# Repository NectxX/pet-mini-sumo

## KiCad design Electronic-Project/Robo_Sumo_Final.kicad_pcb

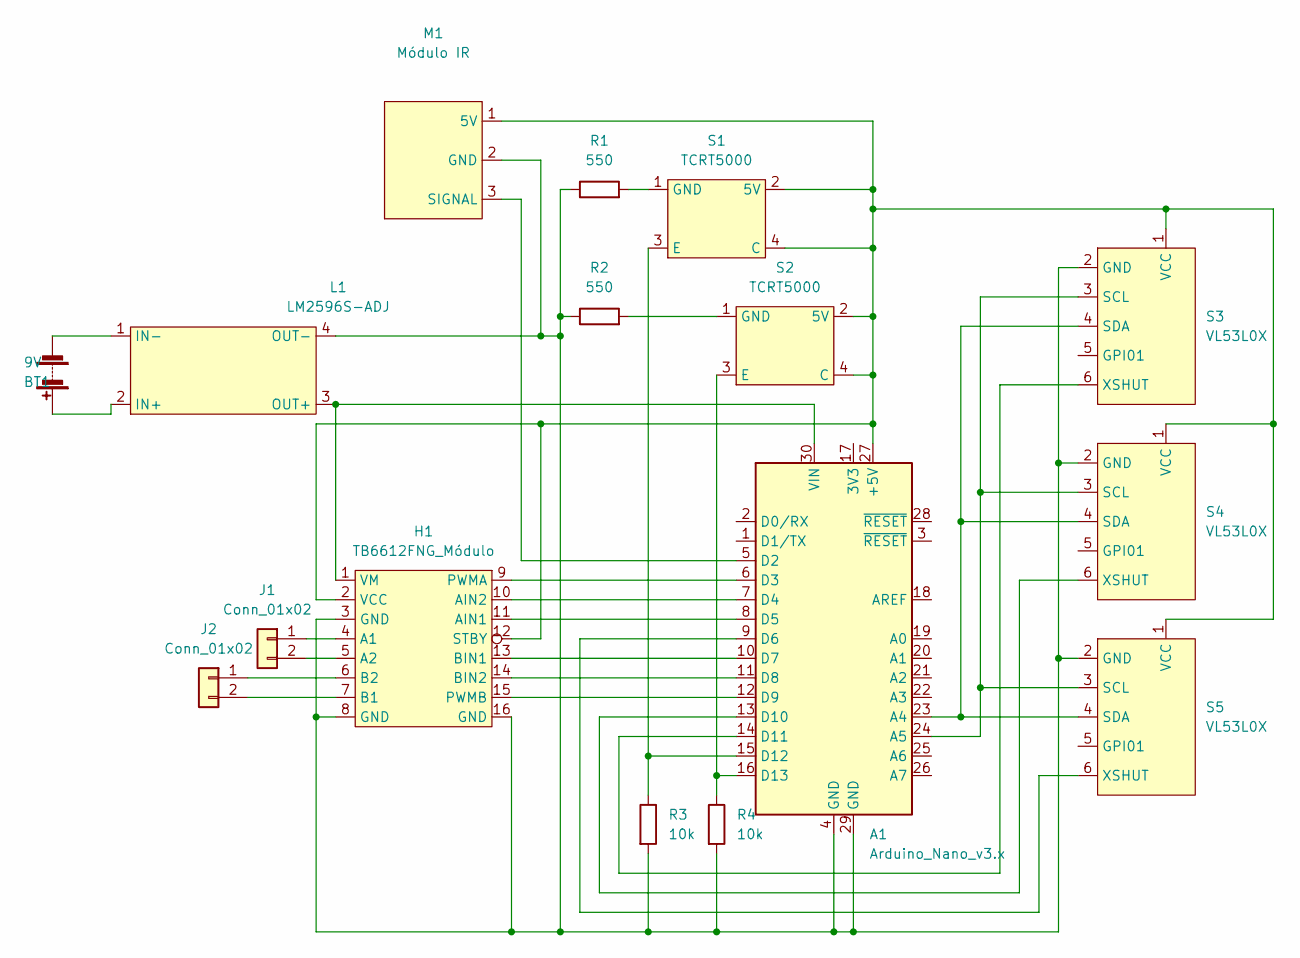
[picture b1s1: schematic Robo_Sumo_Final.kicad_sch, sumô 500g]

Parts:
A1: Arduino_Nano_v3.x; Arduino_Nano
BT1: 9V; PinHeader_1x02_P2.54mm_Vertical
H1: TB6612FNG_Módulo; TB6612FNG
J1, J2: Conn_01x02; PinHeader_1x02_P2.54mm_Vertical
L1: LM2596S-ADJ; LM2596
M1: Módulo IR; PinHeader_1x03_P2.54mm_Vertical
R1, R2: 550; R_Axial_DIN0207_L6.3mm_D2.5mm_P15.24mm_Horizontal
R3, R4: 10k; R_Axial_DIN0207_L6.3mm_D2.5mm_P15.24mm_Horizontal
S1, S2: TCRT5000
S3, S4, S5: VL53L0X; PinHeader_1x06_P2.54mm_Vertical

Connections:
unnamed: A1.5 (D2), M1.3 (SIGNAL)
unnamed: A1.6 (D3), H1.9 (PWMA)
unnamed: A1.7 (D4), H1.10 (AIN2)
unnamed: A1.8 (D5), H1.11 (AIN1)
unnamed: A1.9 (D6), S5.6 (XSHUT)
unnamed: A1.10 (D7), H1.13 (BIN1)
unnamed: A1.11 (D8), H1.14 (BIN2)
unnamed: A1.12 (D9), H1.15 (PWMB)
unnamed: A1.13 (D10), S4.6 (XSHUT)
unnamed: A1.14 (D11), S3.6 (XSHUT)
unnamed: A1.15 (D12), R3.1, S1.3 (E)
unnamed: A1.16 (D13), R4.1, S2.3 (E)
unnamed: A1.23 (A4), S3.4 (SDA), S4.4 (SDA), S5.4 (SDA)
unnamed: A1.24 (A5), S3.3 (SCL), S4.3 (SCL), S5.3 (SCL)
unnamed: A1.27 (+5V), H1.2 (VCC), H1.12 (STBY), M1.1 (5V), S1.2 (5V), S1.4 (C), S2.2 (5V), S2.4 (C), S3.1 (VCC), S4.1 (VCC), S5.1 (VCC)
unnamed: A1.4 (GND), A1.29 (GND), H1.3 (GND), H1.8 (GND), H1.16 (GND), L1.4 (OUT-), M1.2 (GND), R1.1, R2.1, R3.2, R4.2, S3.2 (GND), S4.2 (GND), S5.2 (GND)
unnamed: A1.30 (VIN), H1.1 (VM), L1.3 (OUT+)
unnamed: BT1.1 (+), L1.2 (IN+)
unnamed: BT1.2 (-), L1.1 (IN-)
unnamed: H1.4 (A1), J1.1
unnamed: H1.5 (A2), J1.2
unnamed: H1.6 (B2), J2.1
unnamed: H1.7 (B1), J2.2
unnamed: R1.2, S1.1 (GND)
unnamed: R2.2, S2.1 (GND)

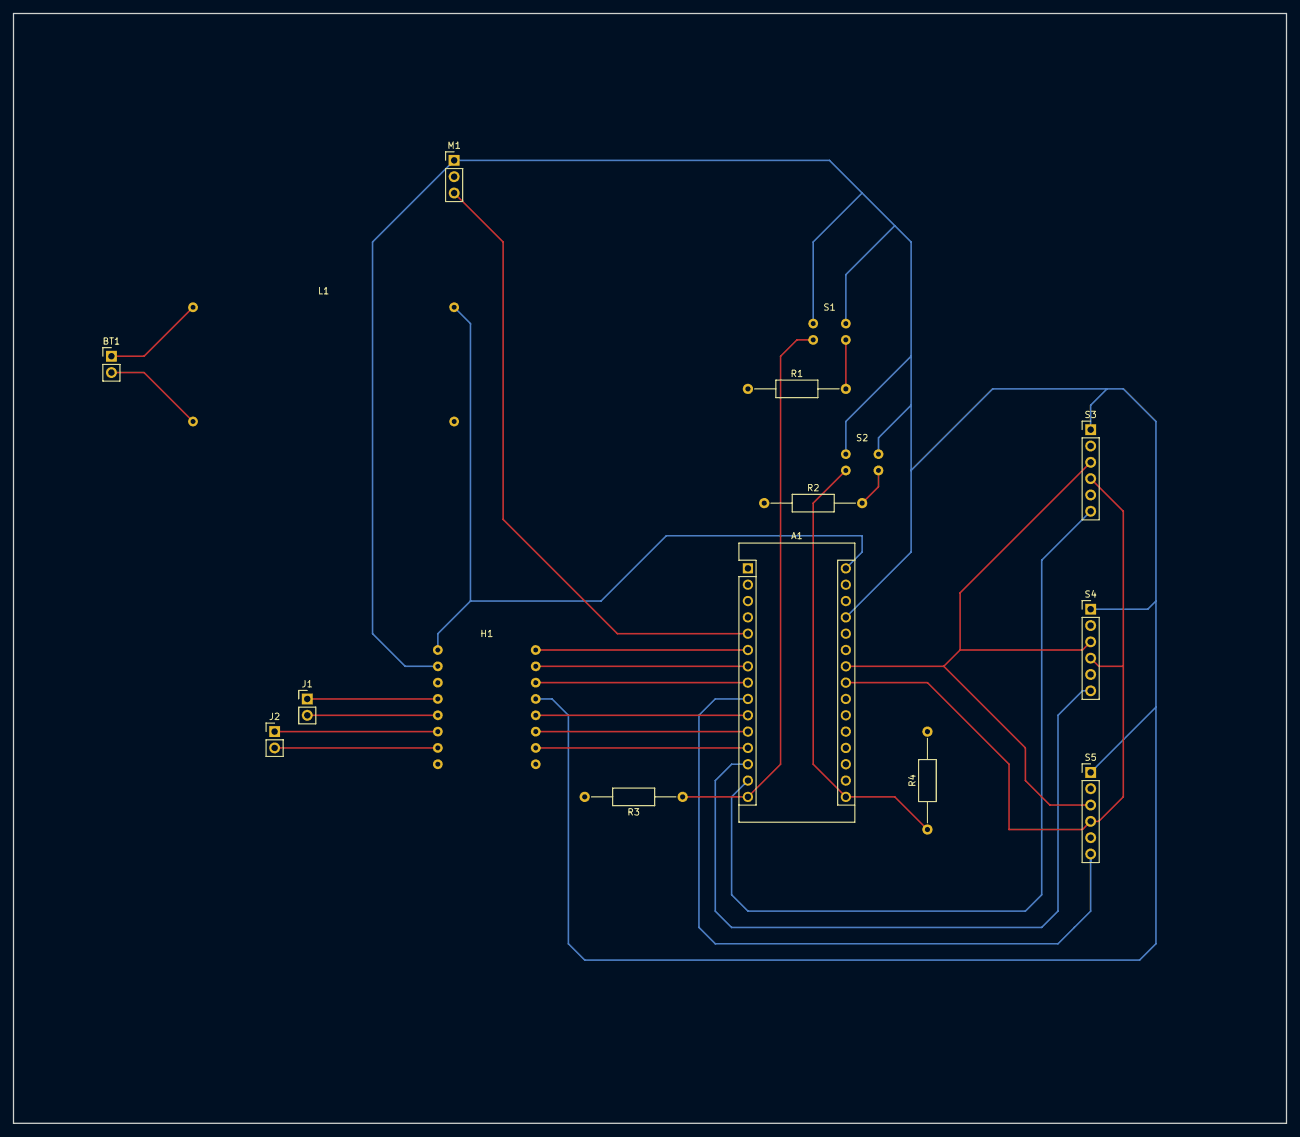
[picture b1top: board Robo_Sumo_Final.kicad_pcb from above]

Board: 2 copper layers, 198.1 x 172.7 mm, 16 parts (0 on the bottom side), 25 nets.

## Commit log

2022-06-24 adding kicad-file
2022-06-24 texto de teste
2022-06-24 modifing file
2022-06-24 adding project tree
2022-06-24 código ponte h
2022-06-26 Colocando projeto PCB e Esquematico
